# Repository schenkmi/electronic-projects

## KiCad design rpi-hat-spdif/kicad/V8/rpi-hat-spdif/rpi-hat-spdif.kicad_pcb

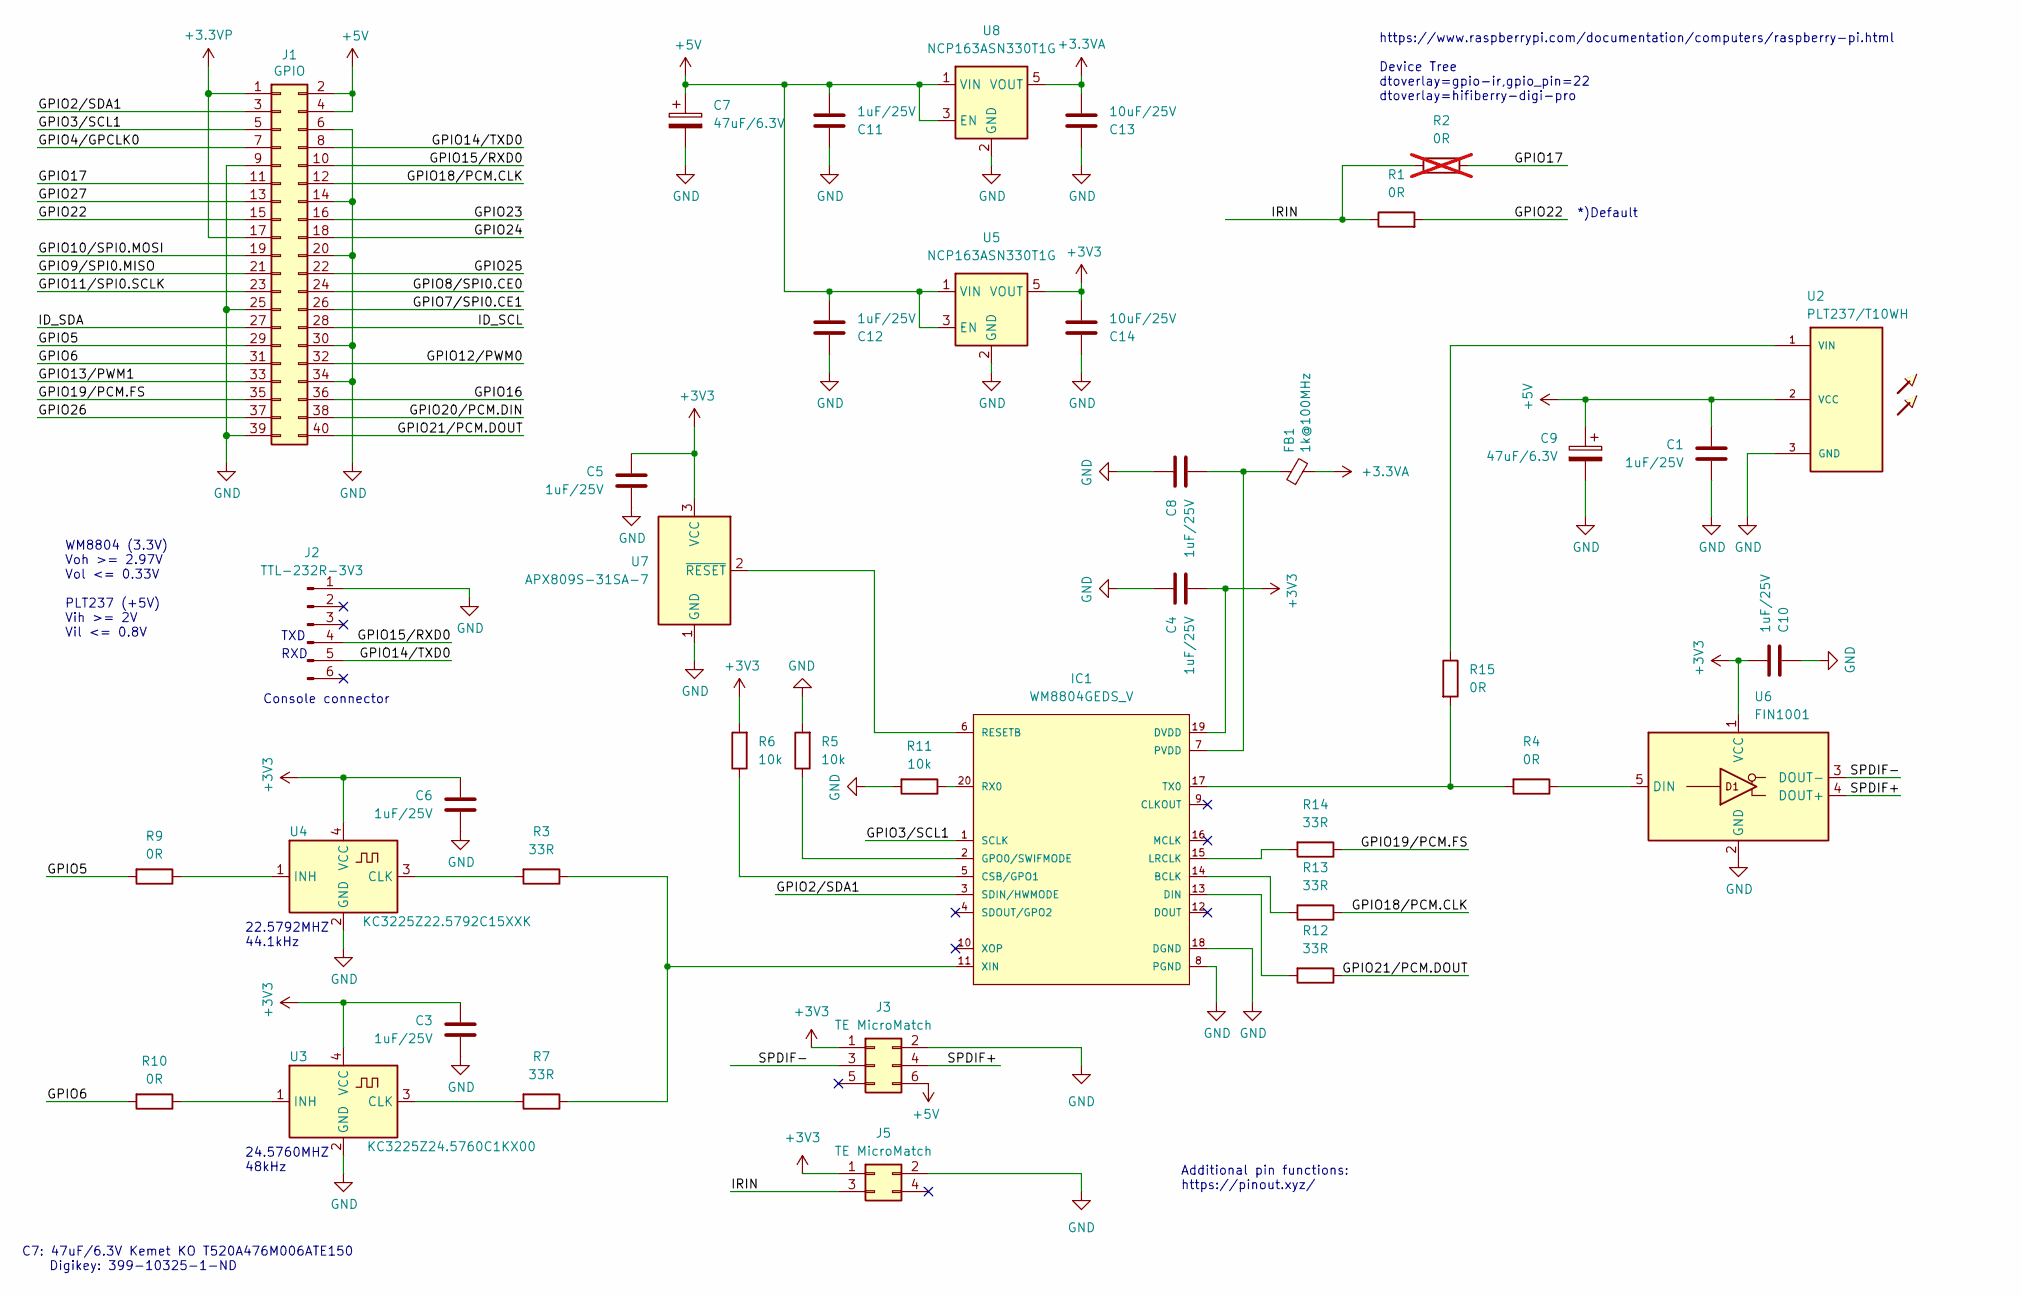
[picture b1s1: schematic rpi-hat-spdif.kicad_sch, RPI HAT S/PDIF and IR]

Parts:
C1, C4, C8, C10, C11, C12: 1uF/25V; C_0603_1608Metric_Pad1.08x0.95mm_HandSolder
C3, C5, C6: 1uF/25V; C_0603_1608Metric
C7, C9: 47uF/6.3V; C_1206_3216Metric_Pad1.33x1.80mm_HandSolder
C13, C14: 10uF/25V; C_1206_3216Metric_Pad1.33x1.80mm_HandSolder
FB1: 1k@100MHz; R_0603_1608Metric_Pad0.98x0.95mm_HandSolder
IC1: WM8804GEDS_V; SSOP-20_5.3x7.2mm_P0.65mm
J1: GPIO; PinSocket_2x20_P2.54mm_Vertical
J2: TTL-232R-3V3; PinHeader_1x06_P2.54mm_Vertical
J3: TE MicroMatch; TE_Micro-MaTch_215079-6_2x03_P1.27mm_Vertical
J5: TE MicroMatch; TE_Micro-MaTch_215079-4_2x02_P1.27mm_Vertical
R1, R4, R9, R10, R15: 0R; R_0603_1608Metric_Pad0.98x0.95mm_HandSolder
R2: 0R; R_0603_1608Metric_Pad0.98x0.95mm_HandSolder; not fitted
R3, R7, R12, R13, R14: 33R; R_0603_1608Metric_Pad0.98x0.95mm_HandSolder
R5, R6, R11: 10k; R_0603_1608Metric_Pad0.98x0.95mm_HandSolder
U2: PLT237/T10WH; PLR135-T10_PLT133-T10W
U3: KC3225Z24.5760C1KX00; Crystal_SMD_3225-4Pin_3.2x2.5mm_HandSoldering
U4: KC3225Z22.5792C15XXK; Crystal_SMD_3225-4Pin_3.2x2.5mm_HandSoldering
U5, U8: NCP163ASN330T1G; SOT-23-5
U6: FIN1001; SOT-23-5_HandSoldering; Part Number FIN1001M5X
U7: APX809S-31SA-7; SOT-23

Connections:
+3.3VA: C13.2, FB1.2, U8.5 (VOUT)
+3.3VP: J1.1, J1.17
+3V3: C3.1, C4.2, C5.1, C6.1, C10.2, C14.2, IC1.19 (DVDD), J3.1, J5.1, R6.2, U3.4 (VCC), U4.4 (VCC), U5.5 (VOUT), U6.1 (VCC), U7.3 (VCC)
+5V: C1.1, C7.1, C9.1, C11.2, C12.2, J1.2, J1.4, J3.6, U2.2 (VCC), U5.1 (VIN), U5.3 (EN), U8.1 (VIN), U8.3 (EN)
/GPIO2/SDA1: IC1.3 (SDIN/HWMODE), J1.3
/GPIO3/SCL1: IC1.1 (SCLK), J1.5
/GPIO4/GPCLK0: J1.7
/GPIO5: J1.29, R9.2
/GPIO6: J1.31, R10.2
/GPIO7/SPI0.CE1: J1.26
/GPIO8/SPI0.CE0: J1.24
/GPIO9/SPI0.MISO: J1.21
/GPIO10/SPI0.MOSI: J1.19
/GPIO11/SPI0.SCLK: J1.23
/GPIO12/PWM0: J1.32
/GPIO13/PWM1: J1.33
/GPIO14/TXD0: J1.8, J2.5
/GPIO15/RXD0: J1.10, J2.4
/GPIO16: J1.36
/GPIO17: J1.11, R2.2
/GPIO18/PCM.CLK: J1.12, R13.1
/GPIO19/PCM.FS: J1.35, R14.1
/GPIO20/PCM.DIN: J1.38
/GPIO21/PCM.DOUT: J1.40, R12.1
/GPIO22: J1.15, R1.2
/GPIO23: J1.16
/GPIO24: J1.18
/GPIO25: J1.22
/GPIO26: J1.37
/GPIO27: J1.13
/ID_SCL: J1.28
/ID_SDA: J1.27
/IRIN: J5.3, R1.1, R2.1
/SPDIF+: J3.4, U6.4 (DOUT+)
/SPDIF-: J3.3, U6.3 (DOUT-)
GND: C1.2, C3.2, C4.1, C5.2, C6.2, C7.2, C8.1, C9.2, C10.1, C11.1, C12.1, C13.1, C14.1, IC1.8 (PGND), IC1.18 (DGND), J1.6, J1.9, J1.14, J1.20, J1.25, J1.30, J1.34, J1.39, J2.1, J3.2, J5.2, R5.2, R11.2, U2.3 (GND), U3.2 (GND), U4.2 (GND), U5.2 (GND), U6.2 (GND), U7.1 (GND), U8.2 (GND)
unnamed: IC1.14 (BCLK), R13.2
unnamed: IC1.5 (CSB/GPO1), R6.1
unnamed: IC1.13 (DIN), R12.2
unnamed: IC1.2 (GPO0/SWIFMODE), R5.1
unnamed: IC1.15 (LRCLK), R14.2
unnamed: C8.2, FB1.1, IC1.7 (PVDD)
unnamed: IC1.6 (RESETB), U7.2 (~RESET)
unnamed: IC1.20 (RX0), R11.1
unnamed: IC1.17 (TX0), R4.2, R15.2
unnamed: IC1.11 (XIN), R3.1, R7.1
unnamed: R15.1, U2.1 (VIN)
unnamed: R7.2, U3.3 (CLK)
unnamed: R10.1, U3.1 (INH)
unnamed: R3.2, U4.3 (CLK)
unnamed: R9.1, U4.1 (INH)
unnamed: R4.1, U6.5 (DIN)

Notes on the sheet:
24.5760MHZ 48kHz
TXD
Console connector
https://www.raspberrypi.com/documentation/computers/raspberry-pi.html Device Tree dtoverlay=gpio-ir,gpio_pin=22 dtoverlay=hifiberry-digi-pro
WM8804 (3.3V) Voh >= 2.97V Vol <= 0.33V PLT237 (+5V) Vih >= 2V Vil <= 0.8V
22.5792MHZ 44.1kHz
C7: 47uF/6.3V Kemet KO T520A476M006ATE150 Digikey: ‎399-10325-1-ND‎
RXD
*)Default
Additional pin functions: https://pinout.xyz/

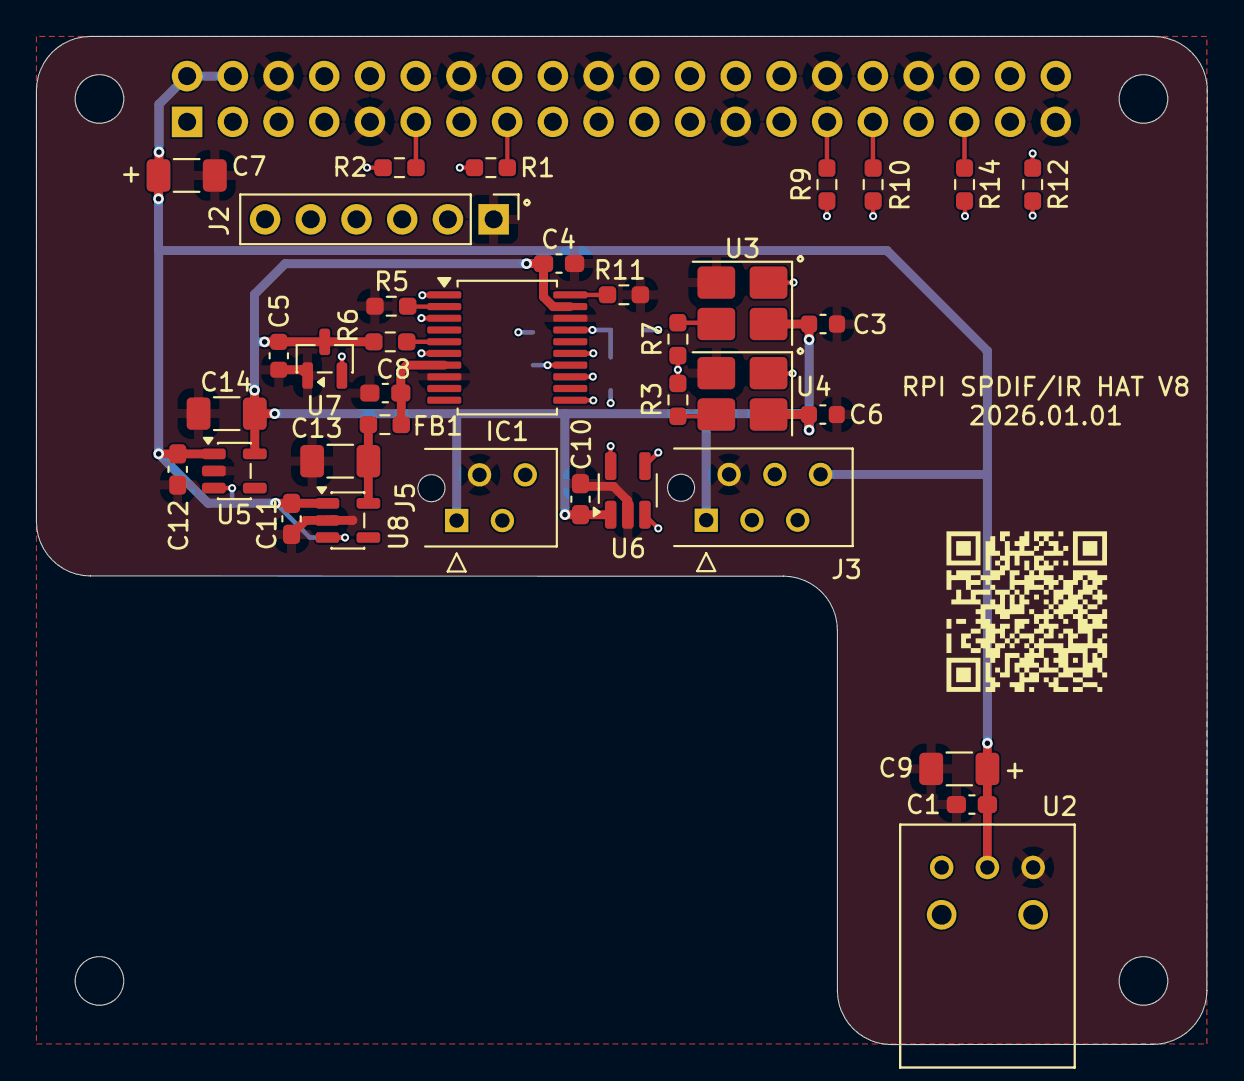
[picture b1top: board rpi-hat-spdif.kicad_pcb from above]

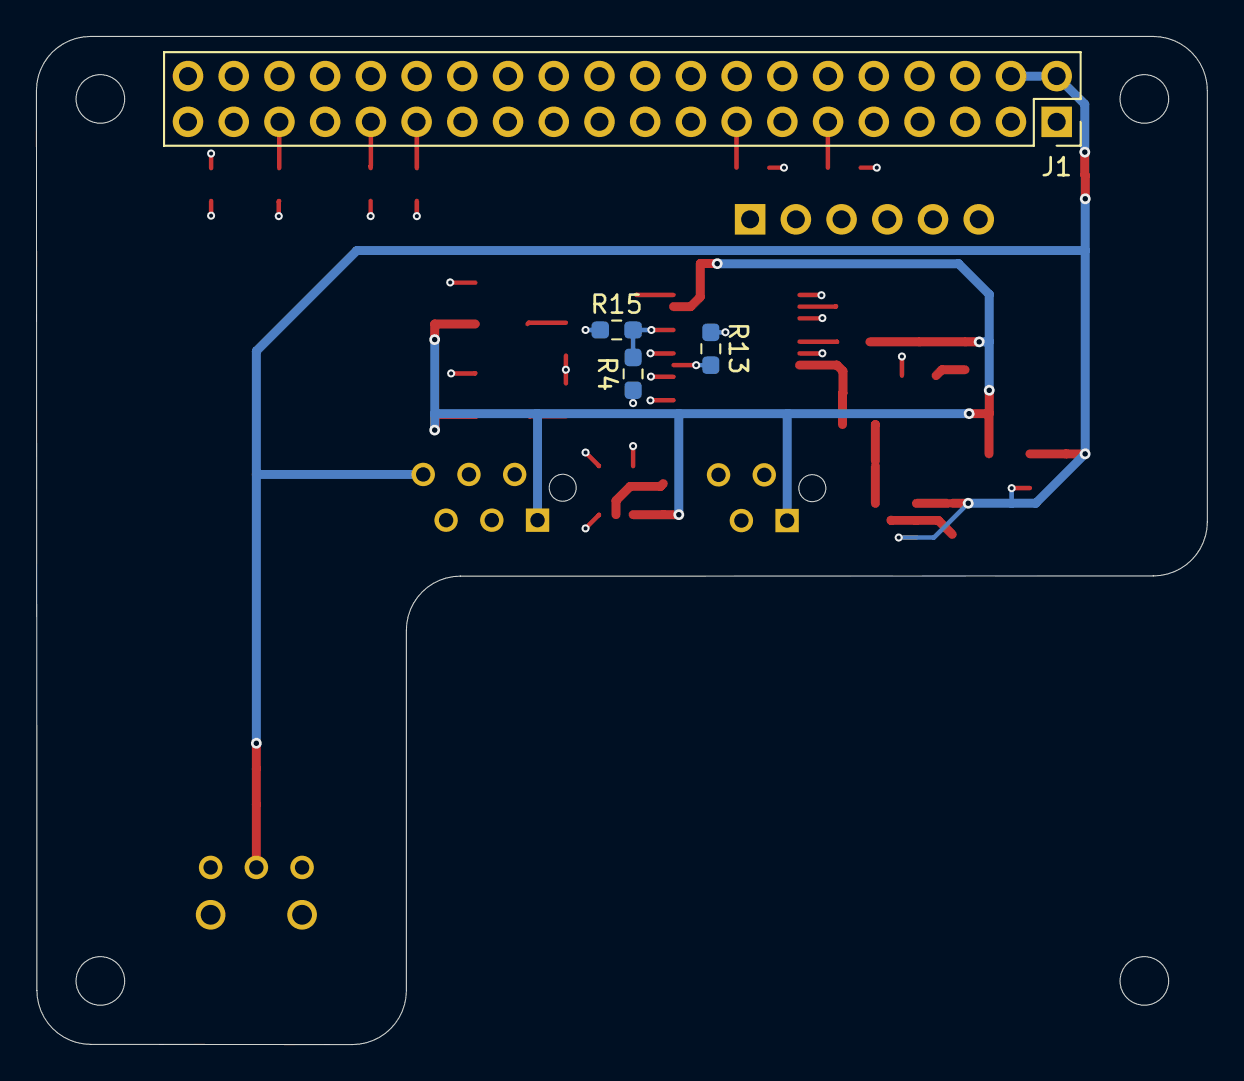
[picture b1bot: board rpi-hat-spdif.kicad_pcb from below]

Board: 4 copper layers, 65.0 x 56.0 mm, 44 parts (4 on the bottom side), 35 nets.

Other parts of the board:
MH1, MH2, MH3, MH4: MountingHole_2.7mm_M2.5

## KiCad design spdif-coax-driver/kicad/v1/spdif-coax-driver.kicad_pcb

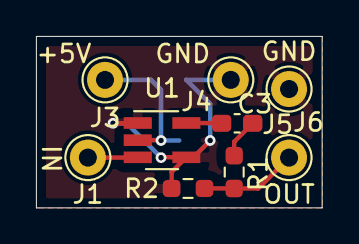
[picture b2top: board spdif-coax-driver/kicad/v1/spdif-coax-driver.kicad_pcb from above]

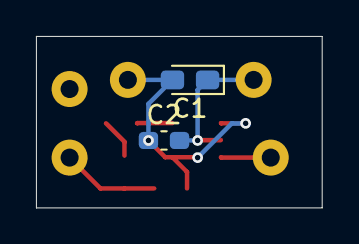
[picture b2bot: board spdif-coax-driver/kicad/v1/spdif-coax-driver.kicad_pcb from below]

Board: 2 copper layers, 15.9 x 9.5 mm, 11 parts (2 on the bottom side), 6 nets.

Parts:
C1: 10uF/10V; CP_EIA-2012-15_AVX-P_Pad1.30x1.05mm_HandSolder
C2, C3: 100nF/50V; C_0603_1608Metric_Pad1.08x0.95mm_HandSolder
J1: IN; Pin_D1.0mm_L10.0mm
J3: +5V; Pin_D1.0mm_L10.0mm
J4: GND; Pin_D1.0mm_L10.0mm
J5: OUT; Pin_D1.0mm_L10.0mm
J6: OUTGND; Pin_D1.0mm_L10.0mm
R1: 300R; R_0603_1608Metric_Pad0.98x0.95mm_HandSolder
R2: 75R; R_0603_1608Metric_Pad0.98x0.95mm_HandSolder
U1: MCP1402T-E_OT; SOT-23-5_HandSoldering

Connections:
+5V: C1.1, C2.2, J3.1, U1.2
GND: C1.2, C2.1, J4.1, J6.1, R2.1, U1.1, U1.4
unnamed: C3.1, R1.2
unnamed: C3.2, U1.5
unnamed: J1.1, U1.3
unnamed: J5.1, R1.1, R2.2

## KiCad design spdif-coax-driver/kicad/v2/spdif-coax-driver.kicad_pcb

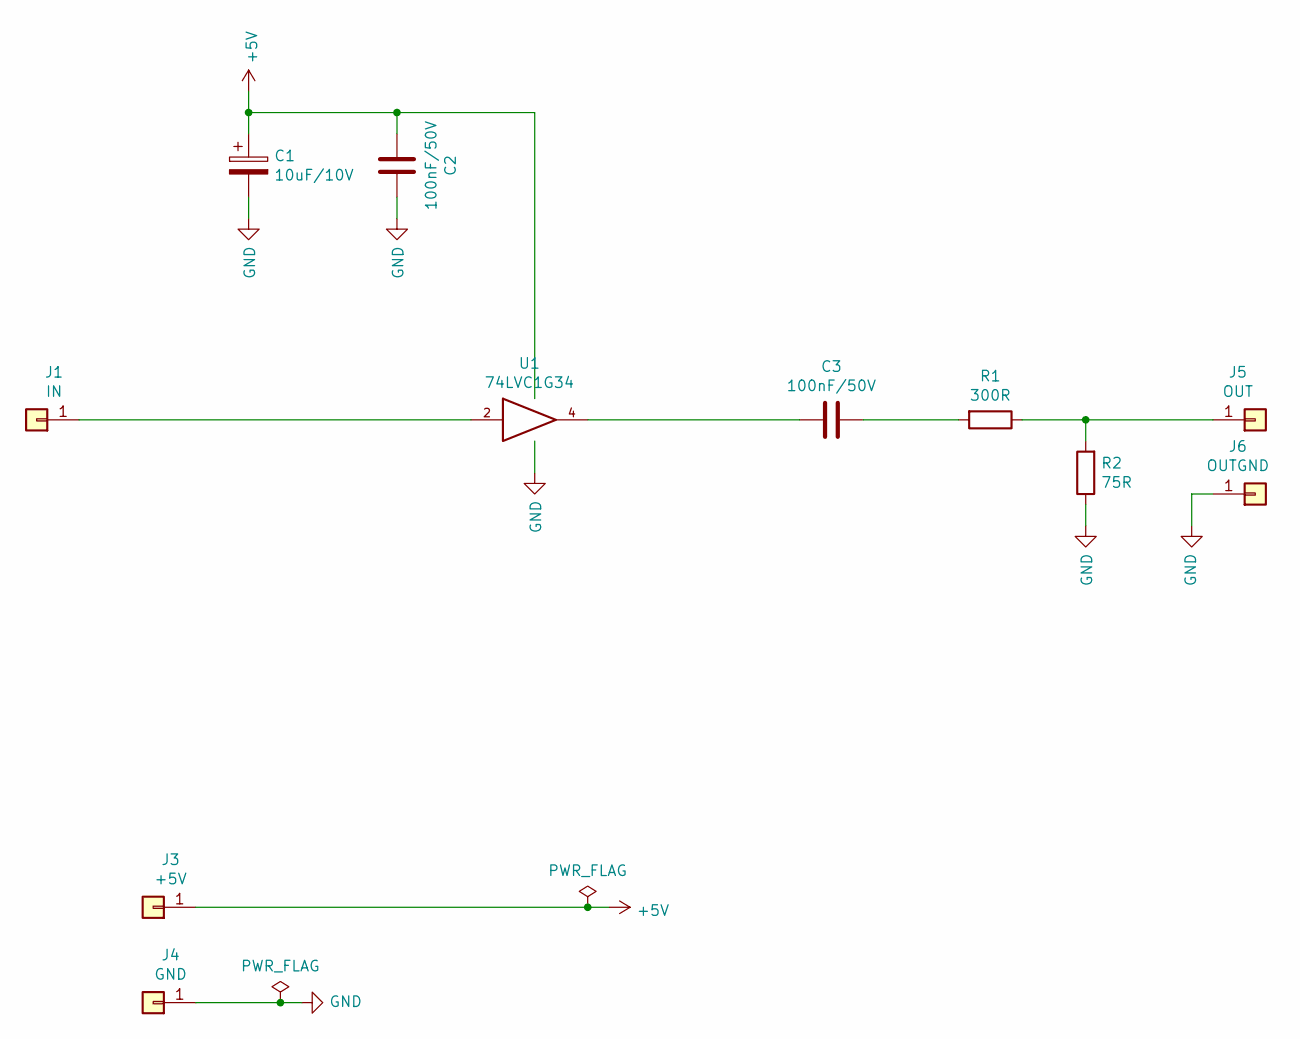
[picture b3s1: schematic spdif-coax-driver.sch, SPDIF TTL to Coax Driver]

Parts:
C1: 10uF/10V; CP_EIA-2012-15_AVX-P_Pad1.30x1.05mm_HandSolder
C2, C3: 100nF/50V; C_0603_1608Metric_Pad1.08x0.95mm_HandSolder
J1: IN; pin-0.6mm
J3: +5V; pin-0.6mm
J4: GND; pin-0.6mm
J5: OUT; pin-0.6mm
J6: OUTGND; pin-0.6mm
R1: 300R; R_0603_1608Metric_Pad0.98x0.95mm_HandSolder
R2: 75R; R_0603_1608Metric_Pad0.98x0.95mm_HandSolder
U1: 74LVC1G34; TSOT-23-5

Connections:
+5V: C1.1, C2.2, J3.1, U1.5 (VCC)
GND: C1.2, C2.1, J4.1, J6.1, R2.1, U1.3 (GND)
unnamed: C3.1, R1.2
unnamed: C3.2, U1.4
unnamed: J1.1, U1.2
unnamed: J5.1, R1.1, R2.2

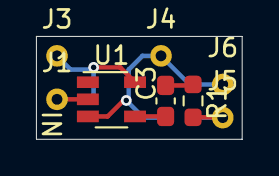
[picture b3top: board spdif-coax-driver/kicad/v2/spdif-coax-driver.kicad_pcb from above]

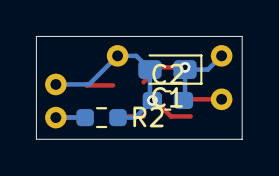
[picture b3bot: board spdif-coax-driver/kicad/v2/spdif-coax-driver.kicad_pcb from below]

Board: 2 copper layers, 11.4 x 5.7 mm, 11 parts (3 on the bottom side), 6 nets.

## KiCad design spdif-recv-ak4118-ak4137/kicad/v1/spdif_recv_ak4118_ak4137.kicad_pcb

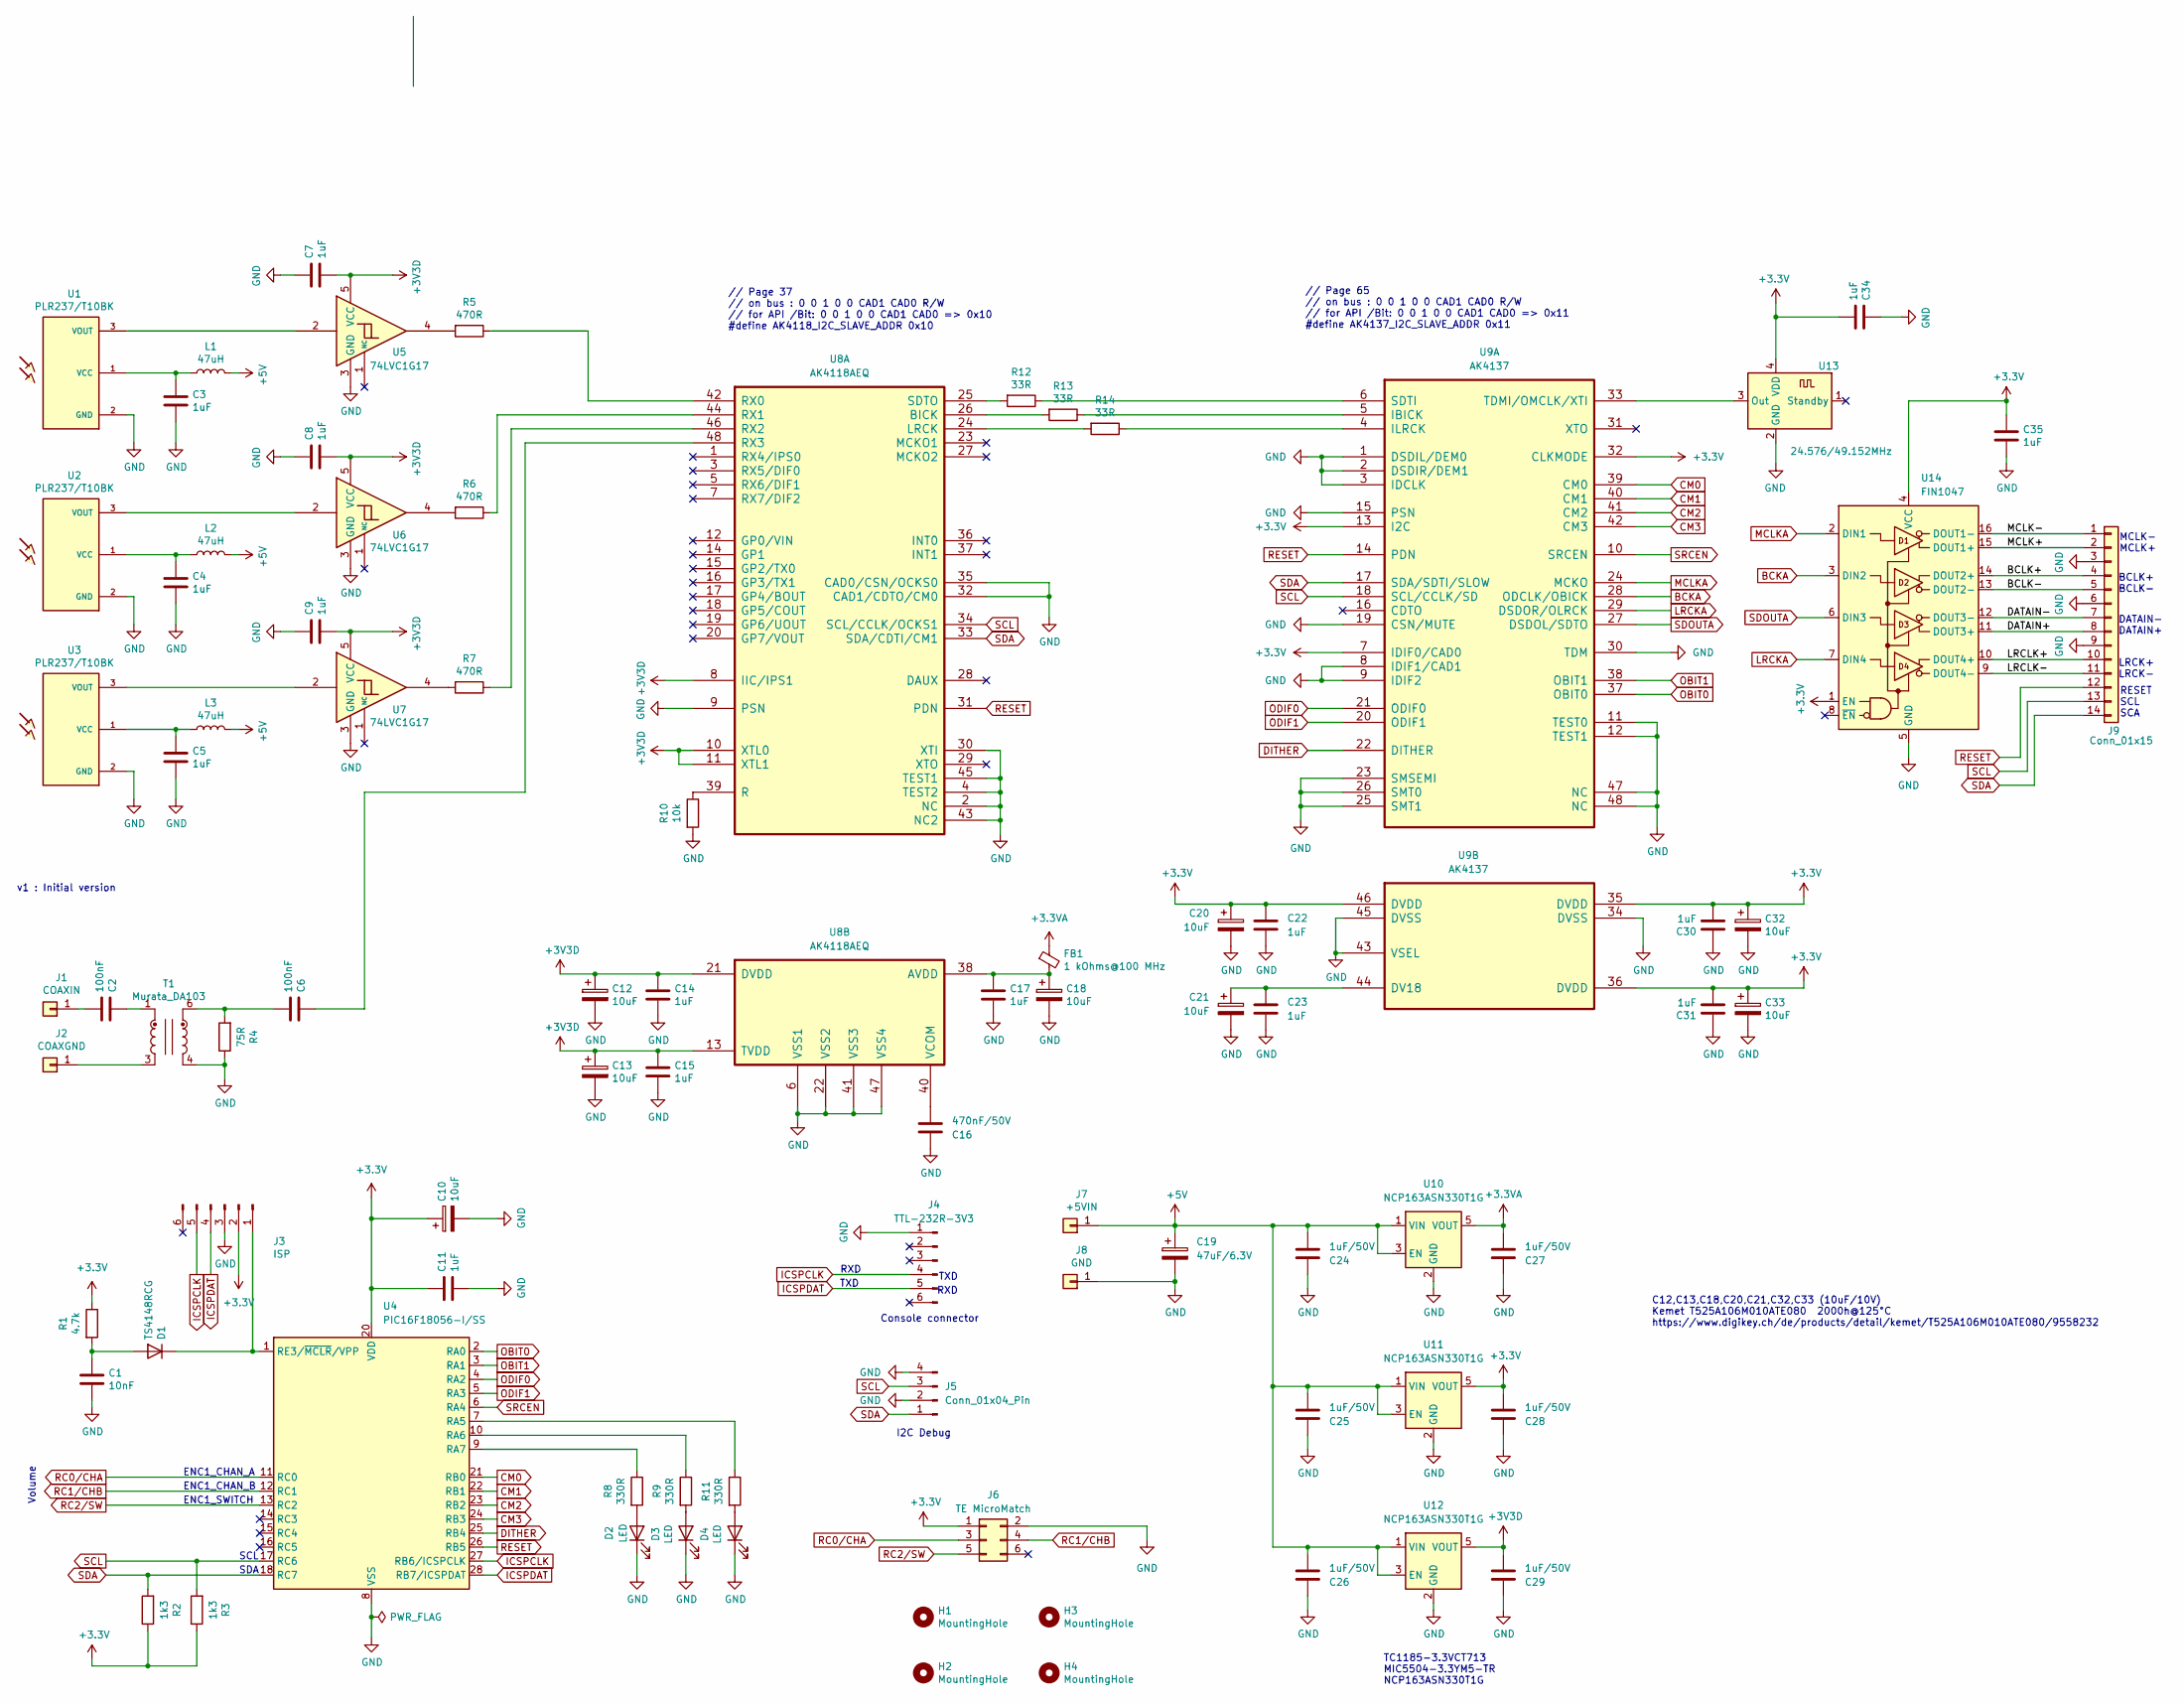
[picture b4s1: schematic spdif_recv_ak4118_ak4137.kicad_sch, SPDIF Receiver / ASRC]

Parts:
C1: 10nF; C_0603_1608Metric_Pad1.08x0.95mm_HandSolder
C2, C6: 100nF; C_0603_1608Metric_Pad1.08x0.95mm_HandSolder
C3, C4, C5, C7, C8, C9, C11, C14, C15, C17, C22, C23, C30, C31, C34, C35: 1uF; C_0603_1608Metric_Pad1.08x0.95mm_HandSolder
C10, C12, C13, C18, C20, C21, C32, C33: 10uF; CP_EIA-2012-12_Kemet-R_HandSolder
C16: 470nF/50V; C_0805_2012Metric_Pad1.18x1.45mm_HandSolder
C19: 47uF/6.3V; C_1206_3216Metric_Pad1.33x1.80mm_HandSolder
C24, C25, C26, C27, C28, C29: 1uF/50V; C_0805_2012Metric_Pad1.18x1.45mm_HandSolder
D1: TS4148RCG; D_0603_1608Metric_Pad1.05x0.95mm_HandSolder
D2, D3, D4: LED; LED_0603_1608Metric_Pad1.05x0.95mm_HandSolder
FB1: 1 kOhms@100 MHz; C_0603_1608Metric_Pad1.08x0.95mm_HandSolder
H1, H2, H3, H4: MountingHole; MountingHole_3.2mm_M3_Pad_Via
J1: COAXIN; Pin_D1.0mm_L10.0mm
J2: COAXGND; Pin_D1.0mm_L10.0mm
J3: ISP; PinHeader_1x06_P2.54mm_Vertical
J4: TTL-232R-3V3; PinHeader_1x06_P2.54mm_Vertical
J5: Conn_01x04_Pin; PinHeader_1x04_P2.54mm_Vertical
J6: TE MicroMatch; TE_Micro-MaTch_215079-6_2x03_P1.27mm_Vertical
J7: +5VIN; Pin_D1.0mm_L10.0mm
J8: GND; Pin_D1.0mm_L10.0mm
J9: Conn_01x15; TE_Micro-MaTch_1-215079-4_2x07_P1.27mm_Vertical
L1, L2, L3: 47uH; L_0805_2012Metric_Pad1.05x1.20mm_HandSolder
R1: 4.7k; R_0603_1608Metric_Pad0.98x0.95mm_HandSolder
R2, R3: 1k3; R_0603_1608Metric_Pad0.98x0.95mm_HandSolder
R4: 75R; R_0603_1608Metric_Pad0.98x0.95mm_HandSolder
R5, R6, R7: 470R; R_0603_1608Metric_Pad0.98x0.95mm_HandSolder
R8, R9, R11: 330R; R_0603_1608Metric_Pad0.98x0.95mm_HandSolder
R10: 10k; R_0603_1608Metric_Pad0.98x0.95mm_HandSolder
R12, R13, R14: 33R; R_0402_1005Metric_Pad0.72x0.64mm_HandSolder
T1: Murata_DA103; DA100J
U1, U2, U3: PLR237/T10BK; PLR135-T10_PLT133-T10W
U4: PIC16F18056-I/SS; SSOP-28_5.3x10.2mm_P0.65mm
U5, U6, U7: 74LVC1G17; SOT-23-5
U8: AK4118AEQ; LQFP-48_7x7mm_P0.5mm
U9: AK4137; LQFP-48_7x7mm_P0.5mm
U10, U11, U12: NCP163ASN330T1G; SOT-23-5
U13: 24.576/49.152MHz; Oscillator_SMD_EuroQuartz_XO32-4Pin_3.2x2.5mm_RotB_HandSold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
U14: FIN1047; TSSOP-16_4.4x5mm_P0.65mm; Part Number FIN1047MTCX

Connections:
+3.3V: C10.1, C11.1, C20.1, C22.2, C28.2, C30.2, C31.2, C32.1, C33.1, C34.1, C35.1, J3.2, J6.1, R1.1, R2.1, R3.1, U4.20 (VDD), U9.7 (IDIF0/CAD0), U9.13 (I2C), U9.32 (CLKMODE), U9.35 (DVDD), U9.36 (DVDD), U9.46 (DVDD), U11.5 (VOUT), U13.4 (VDD), U14.1 (EN), U14.4 (VCC)
+3.3VA: C27.2, FB1.1, U10.5 (VOUT)
+3V3D: C7.1, C8.1, C9.1, C12.1, C13.1, C14.1, C15.1, C29.2, U5.5 (VCC), U6.5 (VCC), U7.5 (VCC), U8.8 (IIC/IPS1), U8.10 (XTL0), U8.11 (XTL1), U8.13 (TVDD), U8.21 (DVDD), U12.5 (VOUT)
+5V: C19.1, C24.2, C25.2, C26.2, J7.1 (Pin_1_1), L1.2, L2.2, L3.2, U10.1 (VIN), U10.3 (EN), U11.1 (VIN), U11.3 (EN), U12.1 (VIN), U12.3 (EN); also elsewhere on the board
/BCLK+: J9.4, U14.14 (DOUT2+)
/BCLK-: J9.5, U14.13 (DOUT2-)
/DATAIN+: J9.8, U14.11 (DOUT3+)
/DATAIN-: J9.7, U14.12 (DOUT3-)
/LRCLK+: J9.10, U14.10 (DOUT4+)
/LRCLK-: J9.11, U14.9 (DOUT4-)
/MCLK+: J9.2, U14.15 (DOUT1+)
/MCLK-: J9.1, U14.16 (DOUT1-)
BCKA: U9.28 (ODCLK/OBICK), U14.3 (DIN2)
CM0: U4.21 (RB0), U9.39 (CM0)
CM1: U4.22 (RB1), U9.40 (CM1)
CM2: U4.23 (RB2), U9.41 (CM2)
CM3: U4.24 (RB3), U9.42 (CM3)
DITHER: U4.25 (RB4), U9.22 (DITHER)
GND: C1.2, C3.1, C4.1, C5.1, C7.2, C8.2, C9.2, C10.2, C11.2, C12.2, C13.2, C14.2, C15.2, C16.1, C17.2, C18.2, C20.2, C21.2, C22.1, C23.1, C24.1, C25.1, C26.1, C27.1, C28.1, C29.1, C30.1, C31.1, C32.2, C33.2, C34.2, C35.2, D2.1 (K), D3.1 (K), D4.1 (K), J3.3, J4.1, J5.2, J5.4, J6.2, J8.1 (Pin_1_1), J9.3, J9.6, J9.9, R4.1, R10.2, T1.4, U1.2 (GND), U2.2 (GND), U3.2 (GND), U4.8 (VSS), U4.19 (VSS), U5.3 (GND), U6.3 (GND), U7.3 (GND), U8.2 (NC), U8.4 (TEST2), U8.6 (VSS1), U8.9 (PSN), U8.22 (VSS2), U8.30 (XTI), U8.32 (CAD1/CDTO/CM0), U8.35 (CAD0/CSN/OCKS0), U8.41 (VSS3), U8.43 (NC2), U8.45 (TEST1), U8.47 (VSS4), U9.1 (DSDIL/DEM0), U9.2 (DSDIR/DEM1), U9.3 (IDCLK), U9.8 (IDIF1/CAD1), U9.9 (IDIF2), U9.11 (TEST0), U9.12 (TEST1), U9.15 (PSN), U9.19 (CSN/MUTE), U9.23 (SMSEMI), U9.25 (SMT1), U9.26 (SMT0), U9.30 (TDM), U9.34 (DVSS), U9.43 (VSEL), U9.45 (DVSS), U9.47 (NC), U9.48 (NC), U10.2 (GND), U11.2 (GND), U12.2 (GND), U13.2 (GND), U14.5 (GND); also elsewhere on the board
ICSPCLK: J3.5, J4.4, U4.27 (RB6/ICSPCLK)
ICSPDAT: J3.4, J4.5, U4.28 (RB7/ICSPDAT)
LRCKA: U9.29 (DSDOR/OLRCK), U14.7 (DIN4)
MCLKA: U9.24 (MCKO), U14.2 (DIN1)
unnamed: C2.2, T1.1
unnamed: C6.1, R4.2, T1.6
unnamed: C1.1, D1.2 (A), R1.2
unnamed: D1.1 (K), J3.1, U4.1 (RE3/~MCLR/VPP)
unnamed: D2.2 (A), R8.2
unnamed: D3.2 (A), R9.2
unnamed: D4.2 (A), R11.2
unnamed: C2.1, J1.1 (Pin_1_1)
unnamed: J2.1 (Pin_1_1), T1.3
unnamed: R5.2, U5.4
unnamed: R6.2, U6.4
unnamed: R7.2, U7.4
unnamed: C3.2, L1.1, U1.1 (VCC)
unnamed: U1.3 (VOUT), U5.2
unnamed: C4.2, L2.1, U2.1 (VCC)
unnamed: U2.3 (VOUT), U6.2
unnamed: C5.2, L3.1, U3.1 (VCC)
unnamed: U3.3 (VOUT), U7.2
unnamed: R11.1, U4.7 (RA5)
unnamed: R9.1, U4.10 (RA6)
unnamed: R8.1, U4.9 (RA7)
unnamed: R13.2, U8.26 (BICK)
unnamed: R14.2, U8.24 (LRCK)
unnamed: R10.1, U8.39 (R)
unnamed: R5.1, U8.42 (RX0)
unnamed: R6.1, U8.44 (RX1)
unnamed: R7.1, U8.46 (RX2)
unnamed: C6.2, U8.48 (RX3)
unnamed: R12.2, U8.25 (SDTO)
unnamed: C17.1, C18.1, FB1.2, U8.38 (AVDD)
unnamed: C16.2, U8.40 (VCOM)
unnamed: R13.1, U9.5 (IBICK)
unnamed: R14.1, U9.4 (ILRCK)
unnamed: R12.1, U9.6 (SDTI)
unnamed: C21.1, C23.2, U9.44 (DV18)
unnamed: U9.33 (TDMI/OMCLK/XTI), U13.3 (Out)
OBIT0: U4.2 (RA0), U9.37 (OBIT0)
OBIT1: U4.3 (RA1), U9.38 (OBIT1)
ODIF0: U4.4 (RA2), U9.21 (ODIF0)
ODIF1: U4.5 (RA3), U9.20 (ODIF1)
RC0/CHA: J6.3, U4.11 (RC0)
RC1/CHB: J6.4, U4.12 (RC1)
RC2/SW: J6.5, U4.13 (RC2)
RESET: J9.12, U4.26 (RB5), U8.31 (PDN), U9.14 (PDN)
SCL: J5.3, J9.13, R3.2, U4.17 (RC6), U8.34 (SCL/CCLK/OCKS1), U9.18 (SCL/CCLK/SD)
SDA: J5.1, J9.14, R2.2, U4.18 (RC7), U8.33 (SDA/CDTI/CM1), U9.17 (SDA/SDTI/SLOW)
SDOUTA: U9.27 (DSDOL/SDTO), U14.6 (DIN3)
SRCEN: U4.6 (RA4), U9.10 (SRCEN)

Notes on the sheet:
I2C Debug
// Page 65 // on bus : 0 0 1 0 0 CAD1 CAD0 R/W // for API /Bit: 0 0 1 0 0 CAD1 CAD0 => 0x11 #define AK4137_I2C_SLAVE_ADDR 0x11
ENC1_CHAN_A
SDA
TC1185-3.3VCT713 MIC5504-3.3YM5-TR NCP163ASN330T1G
MCLK- MCLK+
RXD
DATAIN- DATAIN+
BCLK+ BCLK-
// Page 37 // on bus : 0 0 1 0 0 CAD1 CAD0 R/W // for API /Bit: 0 0 1 0 0 CAD1 CAD0 => 0x10 #define AK4118_I2C_SLAVE_ADDR 0x10
Volume
LRCK+ LRCK-
SCL
v1 : Initial version
RESET SCL SCA
TXD
C12,C13,C18,C20,C21,C32,C33 (10uF/10V) Kemet T525A106M010ATE080 2000h@125°C https://www.digikey.ch/de/products/detail/kemet/T525A106M010ATE080/9558232
ENC1_SWITCH
Console connector
ENC1_CHAN_B

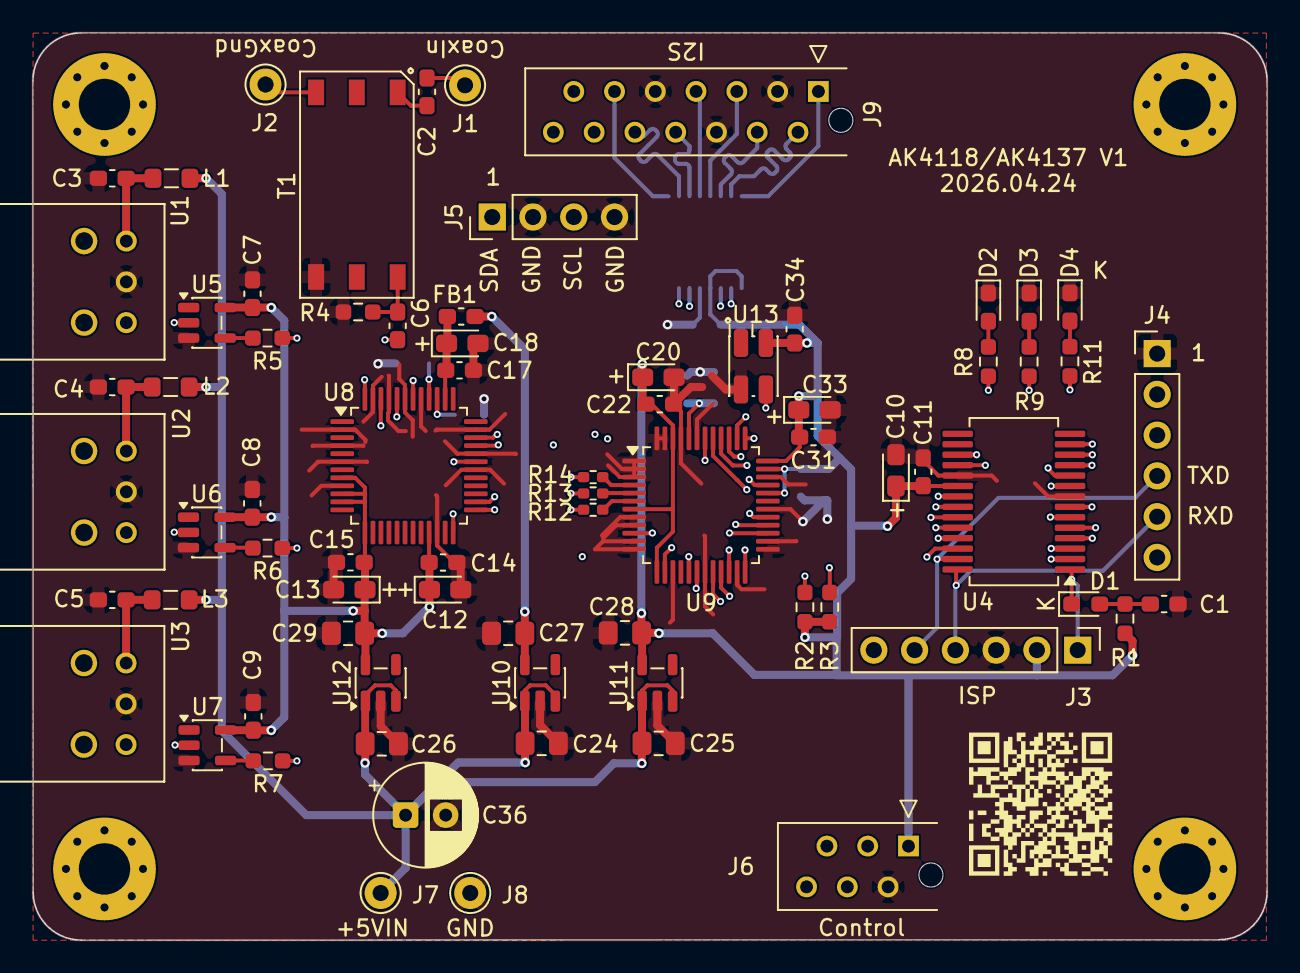
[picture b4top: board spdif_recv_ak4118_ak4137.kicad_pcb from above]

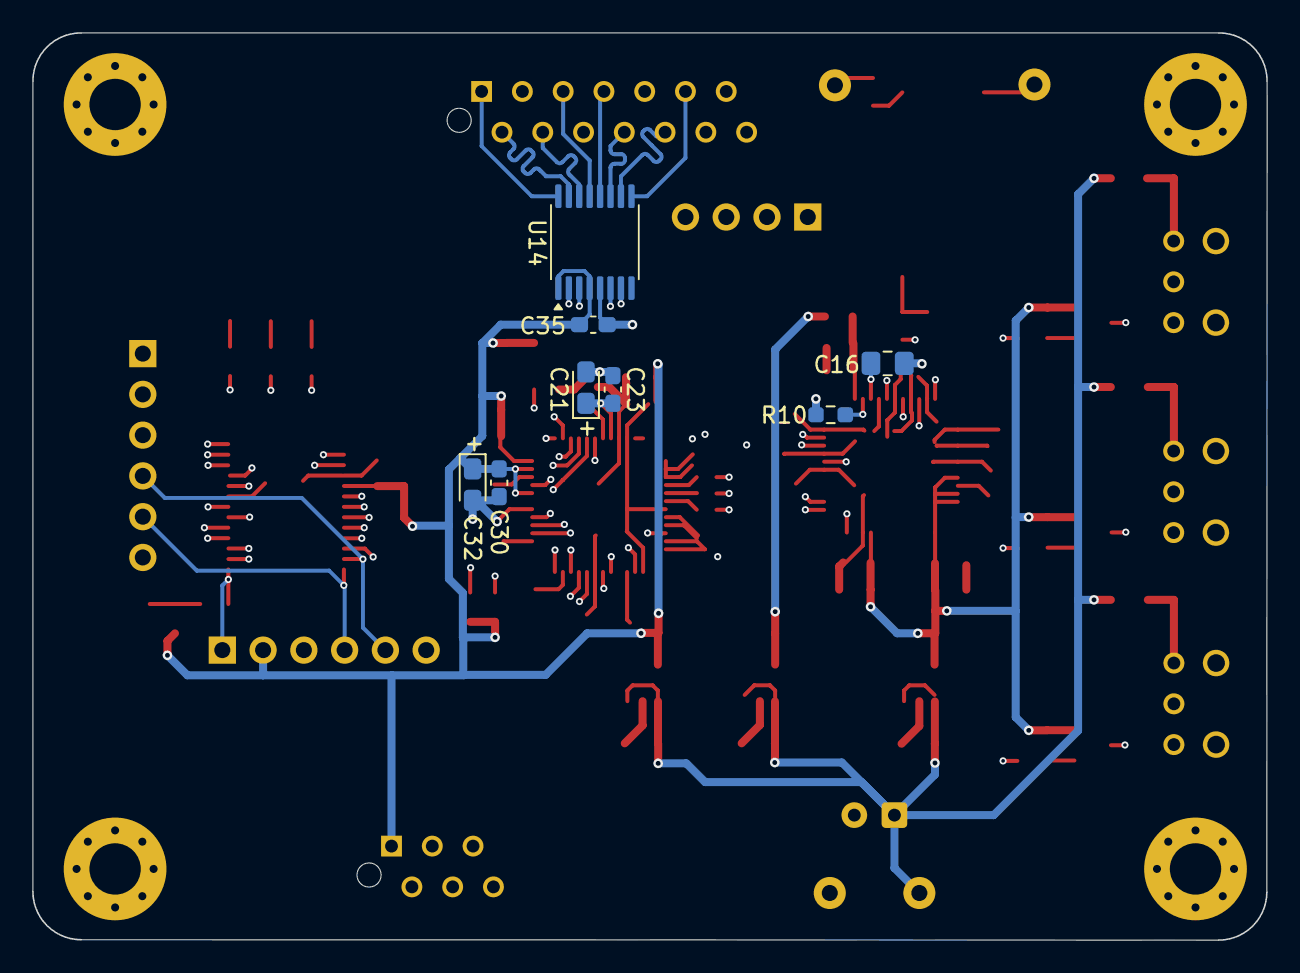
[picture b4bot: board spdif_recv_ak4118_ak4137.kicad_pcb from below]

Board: 4 copper layers, 76.9 x 56.5 mm, 85 parts (8 on the bottom side), 71 nets.

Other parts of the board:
C36: 220uF/10V; CP_Radial_D6.3mm_P2.50mm

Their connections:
+5V: C36.1; also elsewhere on the board
GND: C36.2; also elsewhere on the board
